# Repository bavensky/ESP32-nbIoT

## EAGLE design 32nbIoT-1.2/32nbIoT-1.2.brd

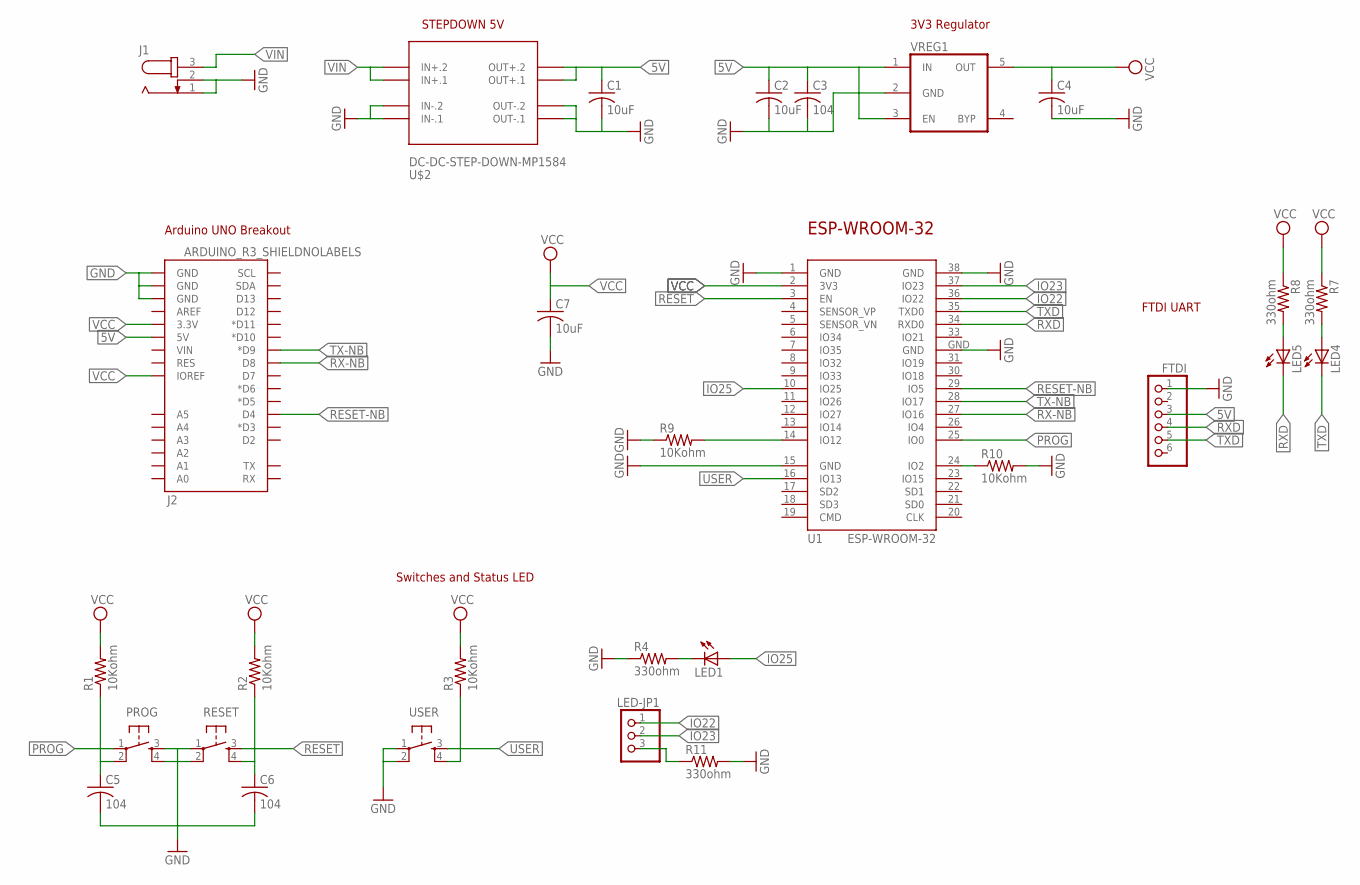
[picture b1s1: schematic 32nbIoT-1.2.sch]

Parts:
C1, C2, C4, C7: 10uF; C0805
C3, C5, C6: 104; C0805
FTDI: PINHD-1X6; 1X06
J1: JACK-PLUG1; SPC4078
J2: ARDUINO_R3_SHIELDNOLABELS; UNO_R3_SHIELD_NOLABELS
LED1, LED4, LED5: LEDCHIPLED_0805; CHIPLED_0805
LED-JP1: PINHD-1X3/90; 1X03/90
PROG: TAC_SWITCHPTH; TACTILE-PTH
R1, R2, R3, R9, R10: 10Kohm; R0805W
R4, R7, R8, R11: 330ohm; R0805W
RESET: TAC_SWITCHPTH; TACTILE-PTH
U1: ESP-WROOM-32
U$2: DC-DC-STEP-DOWN-MP1584
USER: TAC_SWITCHPTH; TACTILE-PTH
VREG1: VREG_5PINS-SOT-23-5; SOT-23-5

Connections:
5V: C1.1, C2.1, C3.1, FTDI.3, J2.5V, U$2.OUT+.1, U$2.OUT+.2, VREG1.1 (IN), VREG1.3 (EN)
GND: C1.2, C2.2, C3.2, C4.2, C5.2, C6.2, C7.2, FTDI.1, J1.1, J1.2, J2.GND@0 (GND), J2.GND@1 (GND), J2.GND@2 (GND), PROG.3, PROG.4, R4.1, R9.1, R10.2, R11.2, RESET.1, RESET.2, U1.1 (GND), U1.15 (GND), U1.38 (GND), U1.GND, U$2.IN-.1, U$2.IN-.2, U$2.OUT-.1, U$2.OUT-.2, USER.1, USER.2, VREG1.2 (GND)
IO22: LED-JP1.1, U1.36 (IO22)
IO23: LED-JP1.2, U1.37 (IO23)
IO25: LED1.A, U1.10 (IO25)
unnamed: R10.1, U1.24 (IO2)
unnamed: R9.2, U1.14 (IO12)
unnamed: LED1.C, R4.2
unnamed: LED-JP1.3, R11.1
unnamed: LED4.A, R7.2
unnamed: LED5.A, R8.2
PROG: C5.1, PROG.1, PROG.2, R1.1, U1.25 (IO0)
RESET: C6.1, R2.1, RESET.3, RESET.4, U1.3 (EN)
RESET-NB: J2.D4, U1.29 (IO5)
RX-NB: J2.D8, U1.27 (IO16)
RXD: FTDI.4, LED5.C, U1.34 (RXD0)
TX-NB: J2.D9 (*D9), U1.28 (IO17)
TXD: FTDI.5, LED4.C, U1.35 (TXD0)
USER: R3.1, U1.16 (IO13), USER.3, USER.4
VCC: C4.1, C7.1, J2.3.3V, J2.IOREF, R1.2, R2.2, R3.2, R7.1, R8.1, U1.2 (3V3), VREG1.5 (OUT)
VIN: J1.3, U$2.IN+.1, U$2.IN+.2

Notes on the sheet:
ESP-WROOM-32
STEPDOWN 5V
3V3 Regulator
Arduino UNO Breakout
FTDI UART
Switches and Status LED

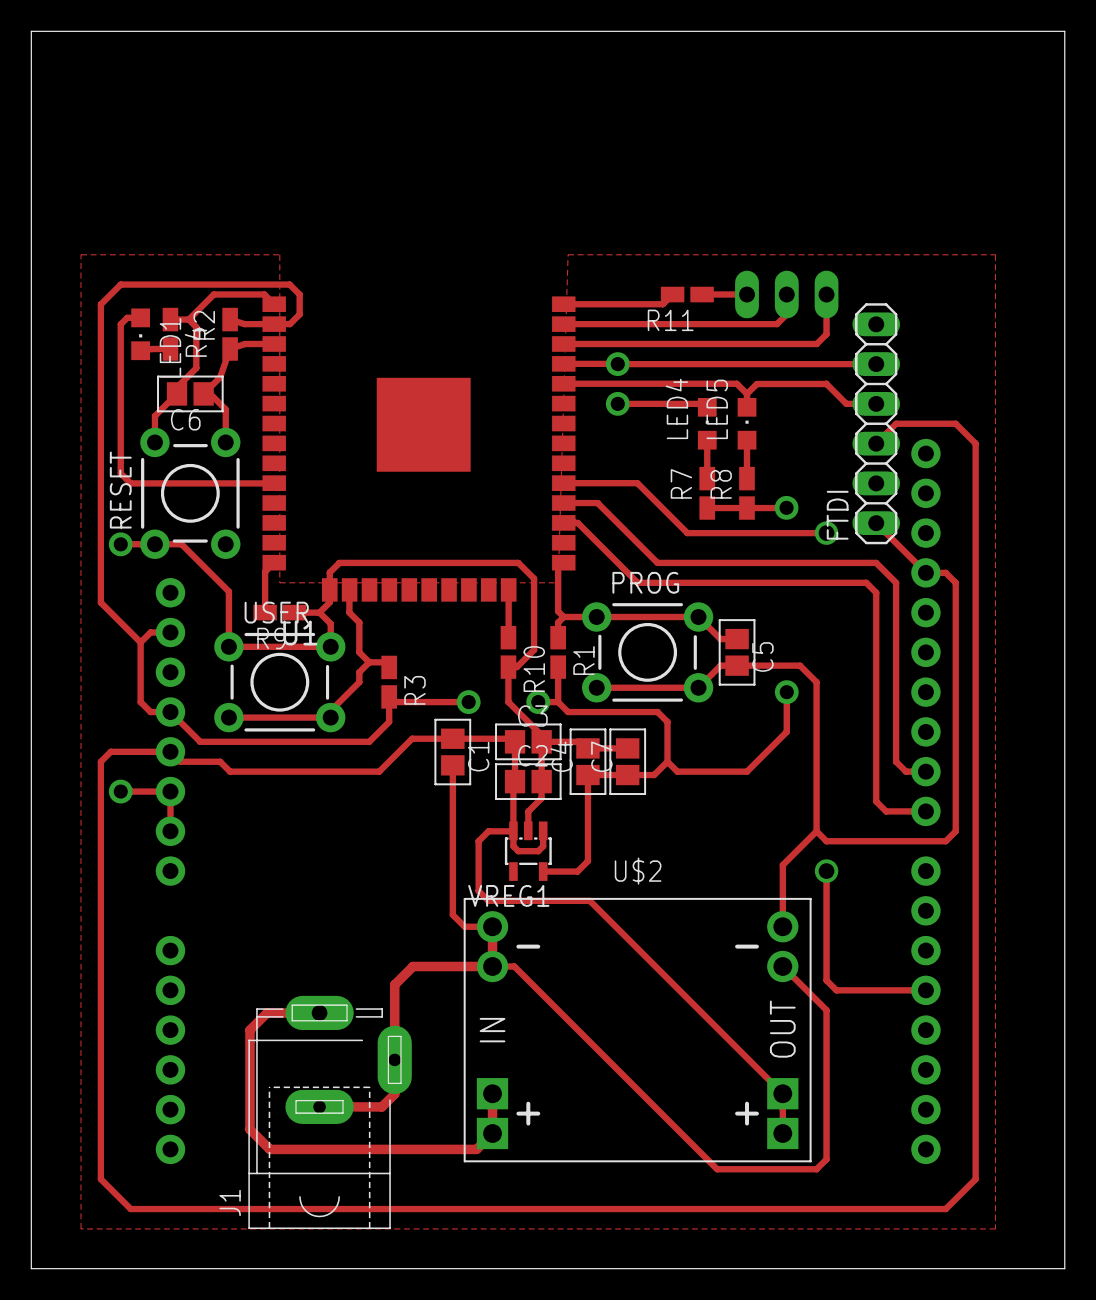
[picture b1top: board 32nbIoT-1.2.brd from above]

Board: 2 copper layers, 66.0 x 79.0 mm, 29 parts (1 on the bottom side), 21 nets.

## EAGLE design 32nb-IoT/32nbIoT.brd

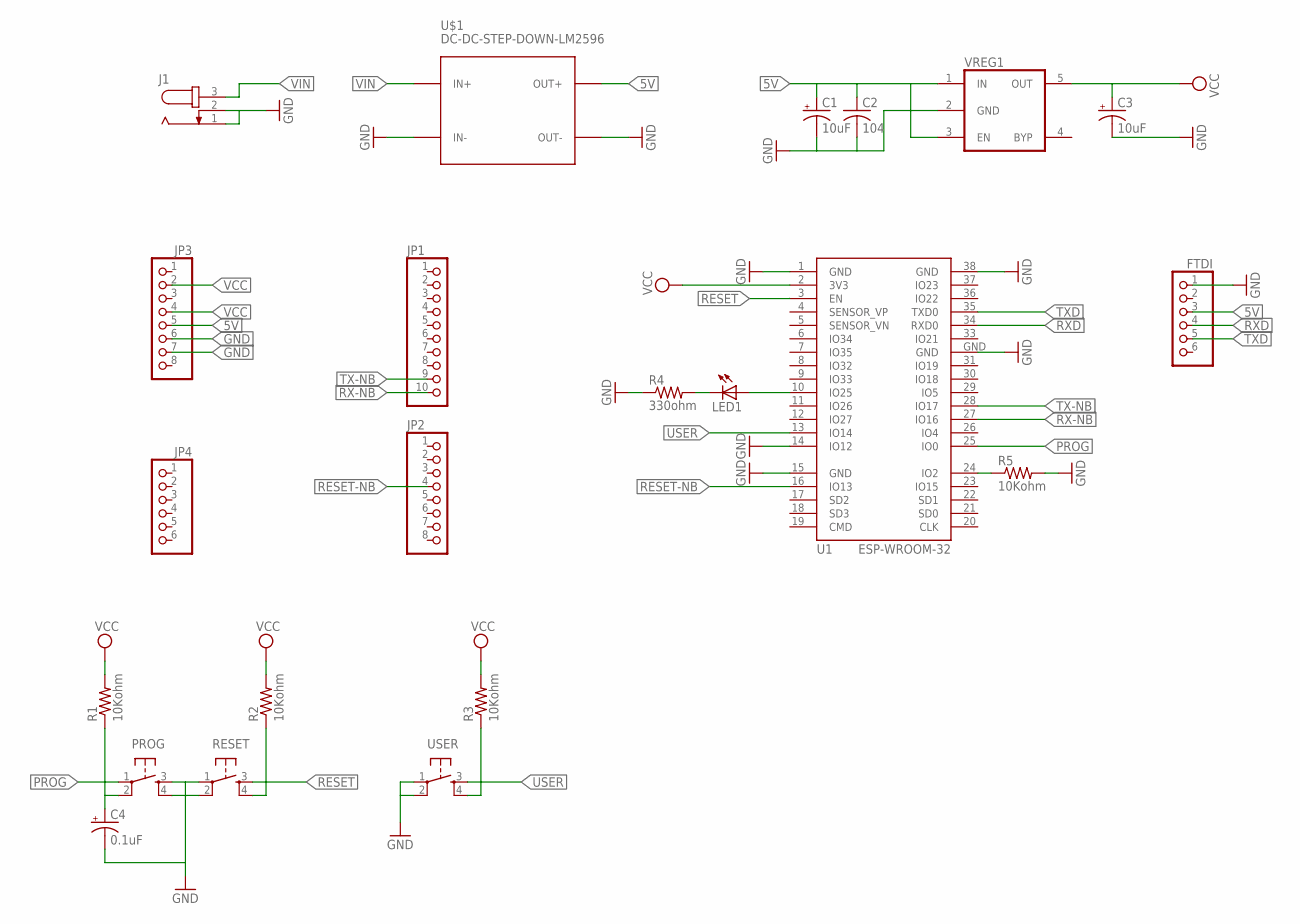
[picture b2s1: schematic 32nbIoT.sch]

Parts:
C1, C3: 10uF; E2,5-6
C2: 104; C050-024X044
C4: 0.1uF; E2,5-6
FTDI: PINHD-1X6; 1X06
J1: JACK-PLUG1; SPC4078
JP1: PINHD-1X10; 1X10
JP2, JP3: PINHD-1X8; 1X08
JP4: PINHD-1X6; 1X06
LED1: LED5MM
PROG: TAC_SWITCHPTH; TACTILE-PTH
R1, R2, R3, R5: 10Kohm; 0207/10
R4: 330ohm; 0207/10
RESET: TAC_SWITCHPTH; TACTILE-PTH
U1: ESP-WROOM-32
U$1: DC-DC-STEP-DOWN-LM2596
USER: TAC_SWITCHPTH; TACTILE-PTH
VREG1: VREG_5PINS-SOT-23-5; SOT-23-5

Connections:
5V: C1.+, C2.1, FTDI.3, JP3.5, U$1.OUT+, VREG1.1 (IN), VREG1.3 (EN)
GND: C1.-, C2.2, C3.-, C4.-, FTDI.1, J1.1, J1.2, JP3.6, JP3.7, PROG.3, PROG.4, R4.1, R5.2, RESET.1, RESET.2, U1.1 (GND), U1.14 (IO12), U1.15 (GND), U1.38 (GND), U1.GND, U$1.IN-, U$1.OUT-, USER.1, USER.2, VREG1.2 (GND)
unnamed: LED1.K (C), R4.2
unnamed: LED1.A, U1.10 (IO25)
unnamed: R5.1, U1.24 (IO2)
PROG: C4.+, PROG.1, PROG.2, R1.1, U1.25 (IO0)
RESET: R2.1, RESET.3, RESET.4, U1.3 (EN)
RESET-NB: JP2.4, U1.16 (IO13)
RX-NB: JP1.10, U1.27 (IO16)
RXD: FTDI.4, U1.34 (RXD0)
TX-NB: JP1.9, U1.28 (IO17)
TXD: FTDI.5, U1.35 (TXD0)
USER: R3.1, U1.13 (IO14), USER.3, USER.4
VCC: C3.+, JP3.2, JP3.4, R1.2, R2.2, R3.2, U1.2 (3V3), VREG1.5 (OUT)
VIN: J1.3, U$1.IN+

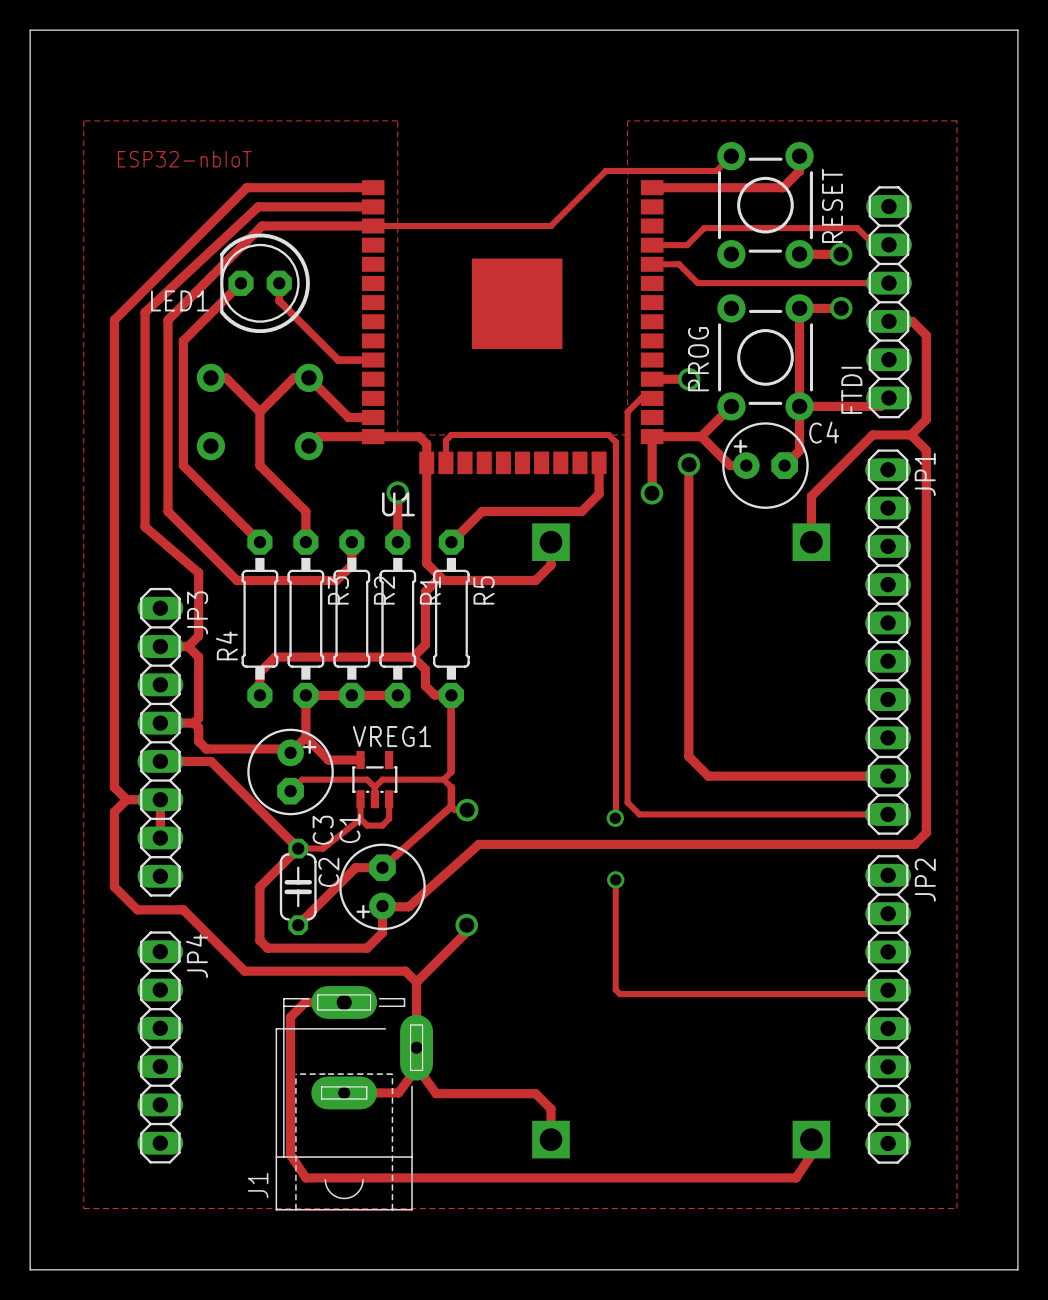
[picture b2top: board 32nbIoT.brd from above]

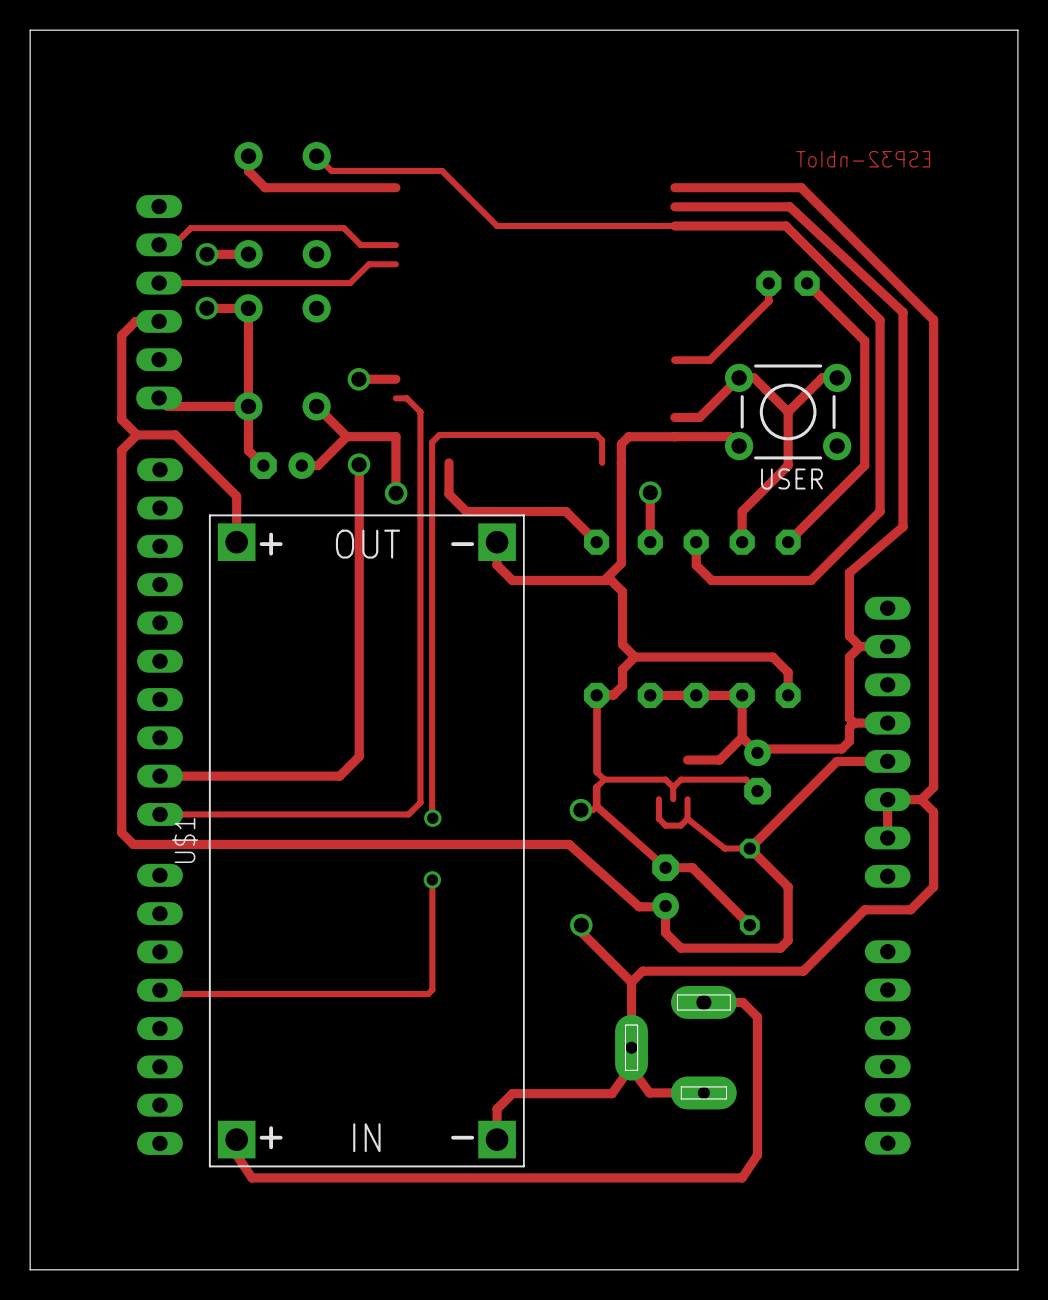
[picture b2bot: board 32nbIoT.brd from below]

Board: 2 copper layers, 65.5 x 82.2 mm, 22 parts (2 on the bottom side), 15 nets.

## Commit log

2018-08-25 add pcb file
2018-09-03 add new pcb version

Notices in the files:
parts and their libraries:
esp32: Creative Commons Attribution-ShareAlike 4.0 International
diy-modules: Released under the Creative Commons Attribution 4.0 International License: http://creativecommons.org/licenses/by/4.0
m-pad-2.1: License : GNU General Public License version 2 (see bottom)
